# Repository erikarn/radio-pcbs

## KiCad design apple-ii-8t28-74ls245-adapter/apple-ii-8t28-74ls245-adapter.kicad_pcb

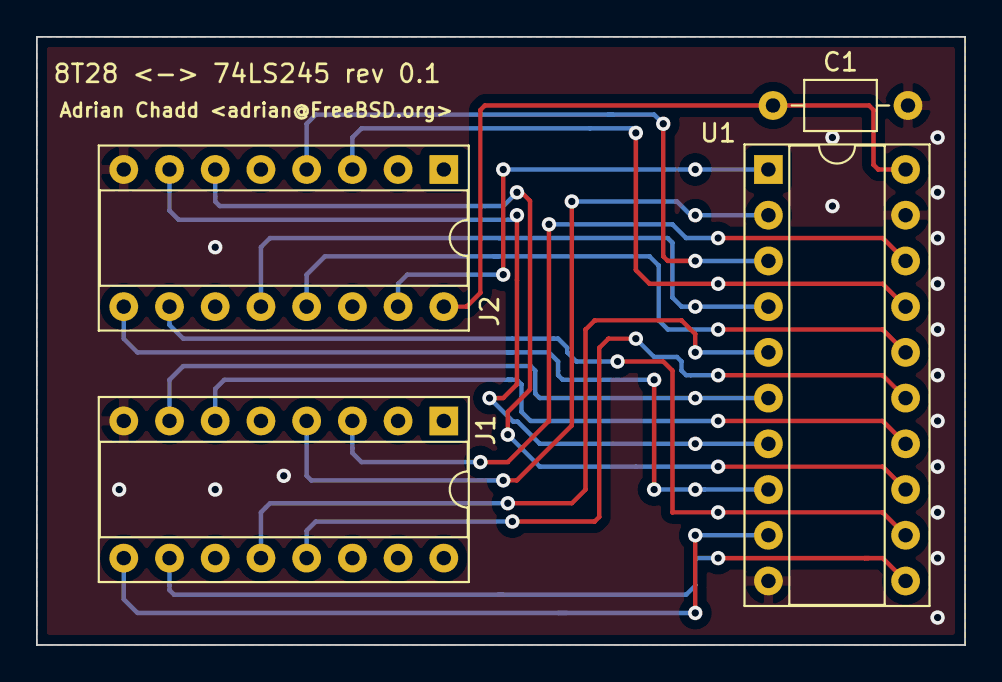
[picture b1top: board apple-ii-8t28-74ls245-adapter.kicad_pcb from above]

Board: 2 copper layers, 51.6 x 33.8 mm, 4 parts (0 on the bottom side), 19 nets.

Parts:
C1: 0.1uF; C_Axial_L3.8mm_D2.6mm_P7.50mm_Horizontal
J1: 8T28 H11; DIP-16_W7.62mm_Socket
J2: 8T28 H10; DIP-16_W7.62mm_Socket
U1: 74LS245; DIP-20_W7.62mm_Socket

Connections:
BUS_D0: J1.4, U1.2
BUS_D1: J2.4, U1.3
BUS_D2: J2.12, U1.4
BUS_D3: J1.12, U1.5
BUS_D4: J1.7, U1.6
BUS_D5: J2.7, U1.7
BUS_D6: J2.9, U1.8
BUS_D7: J1.9, U1.9
CPU_D0: J1.3, U1.18
CPU_D1: J2.3, U1.17
CPU_D2: J2.13, U1.16
CPU_D3: J1.13, U1.15
CPU_D4: J1.6, U1.14
CPU_D5: J2.6, U1.13
CPU_D6: J2.10, U1.12
CPU_D7: J1.10, U1.11
CPU_DIR: J1.15, J2.15, U1.1
GND: C1.2, J1.8, J2.8, U1.10, U1.19
VCC: C1.1, J1.16, J2.16, U1.20

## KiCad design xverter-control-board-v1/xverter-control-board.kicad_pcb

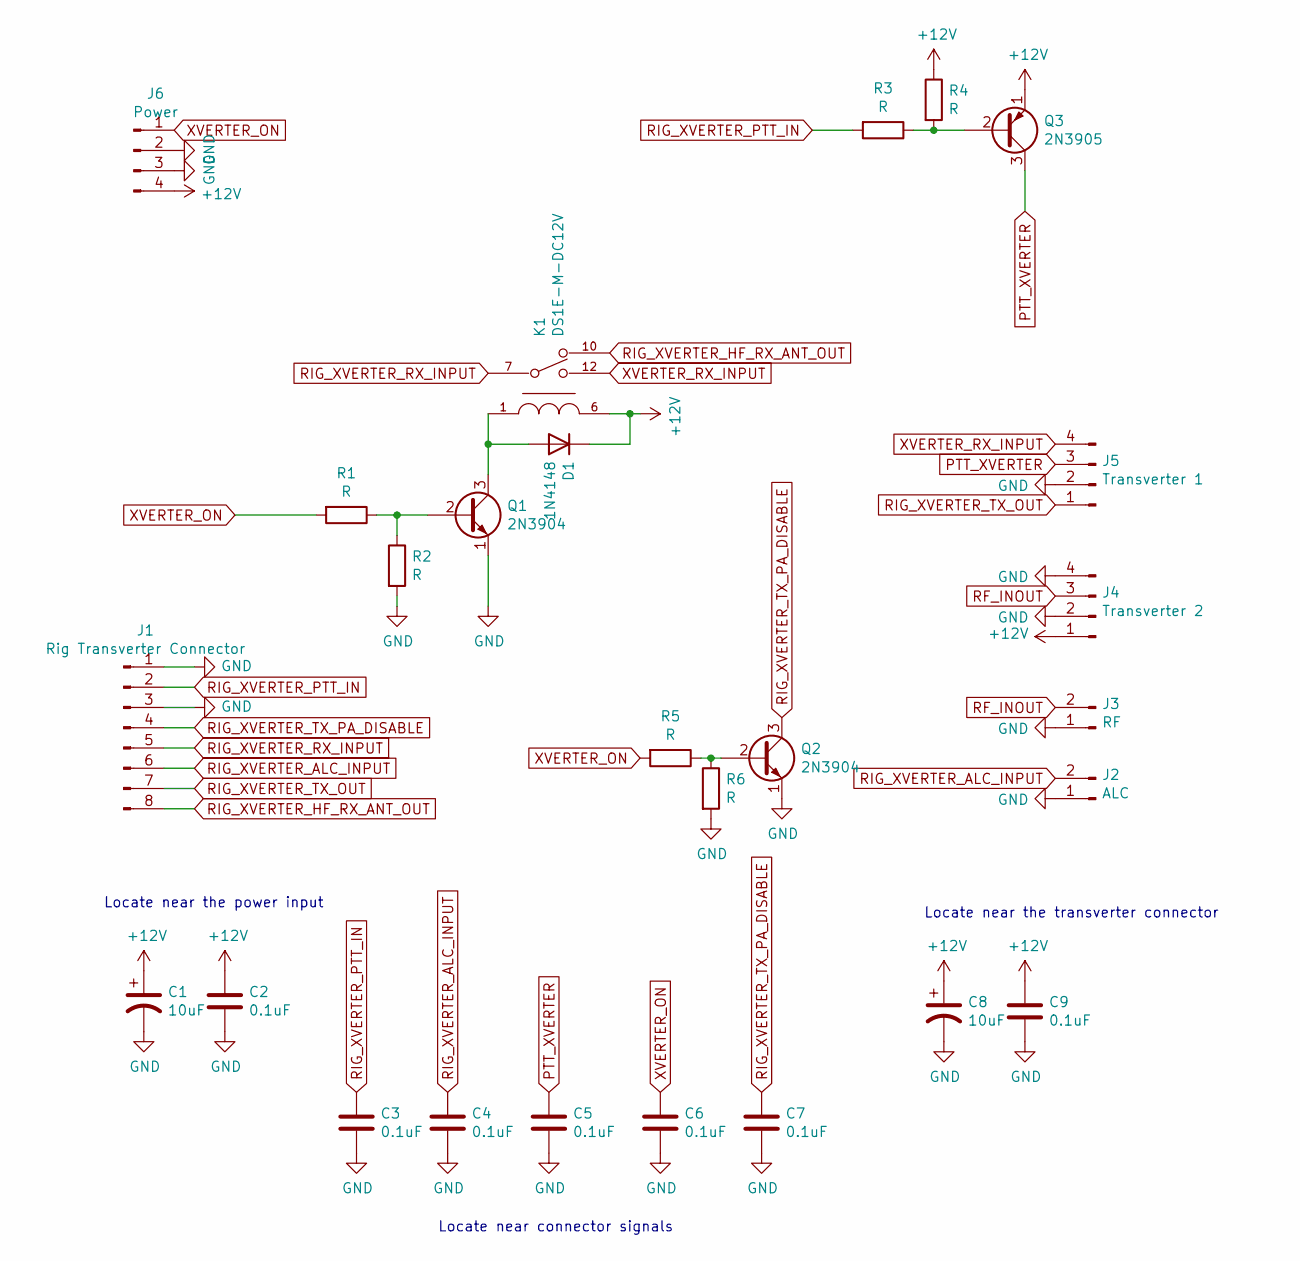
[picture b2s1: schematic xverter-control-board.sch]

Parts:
C1, C8: 10uF; CP_Radial_D5.0mm_P2.00mm
C2, C3, C4, C5, C6, C7, C9: 0.1uF; C_Disc_D3.0mm_W2.0mm_P2.50mm
D1: 1N4148; D_DO-35_SOD27_P7.62mm_Horizontal
J1: Rig Transverter Connector; PinHeader_1x08_P2.54mm_Horizontal
J2: ALC; PinHeader_1x02_P2.54mm_Horizontal
J3: RF; PinHeader_1x02_P2.54mm_Horizontal
J4: Transverter 2; PinHeader_1x04_P2.54mm_Horizontal
J5: Transverter 1; PinHeader_1x04_P2.54mm_Horizontal
J6: Power; PinHeader_1x04_P2.54mm_Horizontal
K1: DS1E-M-DC12V; DIP-12_W7.62mm_LongPads; current rating 3A; voltage rating AC 250V; mouser part number 769-DS1E-M-DC12V; digikey description RELAY GEN PURPOSE SPDT 2A 250V
Q1, Q2: 2N3904; TO-92_Inline
Q3: 2N3905; TO-92_Inline
R1, R2, R3, R4, R5, R6: R; R_Axial_DIN0309_L9.0mm_D3.2mm_P12.70mm_Horizontal

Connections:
+12V: C1.1, C2.1, C8.1, C9.1, D1.1 (K), J4.1, J6.4, K1.6, Q3.1 (E), R4.1
GND: C1.2, C2.2, C3.2, C4.2, C5.2, C6.2, C7.2, C8.2, C9.2, J1.1, J1.3, J2.1, J3.1, J4.2, J4.4, J5.2, J6.2, J6.3, Q1.1 (E), Q2.1 (E), R2.2, R6.2
unnamed: D1.2 (A), K1.1, Q1.3 (C)
unnamed: Q1.2 (B), R1.1, R2.1
unnamed: Q2.2 (B), R5.1, R6.1
unnamed: Q3.2 (B), R3.1, R4.2
PTT_XVERTER: C5.1, J5.3, Q3.3 (C)
RF_INOUT: J3.2, J4.3
RIG_XVERTER_ALC_INPUT: C4.1, J1.6, J2.2
RIG_XVERTER_HF_RX_ANT_OUT: J1.8, K1.10
RIG_XVERTER_PTT_IN: C3.1, J1.2, R3.2
RIG_XVERTER_RX_INPUT: J1.5, K1.7
RIG_XVERTER_TX_OUT: J1.7, J5.1
RIG_XVERTER_TX_PA_DISABLE: C7.1, J1.4, Q2.3 (C)
XVERTER_ON: C6.1, J6.1, R1.2, R5.2
XVERTER_RX_INPUT: J5.4, K1.12

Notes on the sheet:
Locate near the transverter connector
Locate near the power input
Locate near connector signals

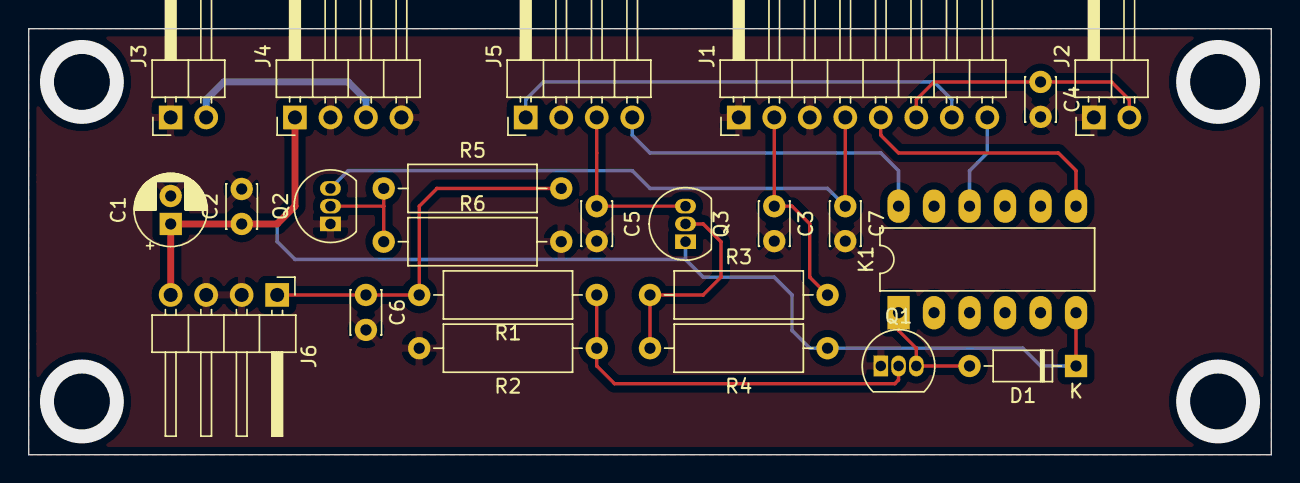
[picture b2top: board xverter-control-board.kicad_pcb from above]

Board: 2 copper layers, 88.9 x 30.5 mm, 24 parts (0 on the bottom side), 16 nets.
